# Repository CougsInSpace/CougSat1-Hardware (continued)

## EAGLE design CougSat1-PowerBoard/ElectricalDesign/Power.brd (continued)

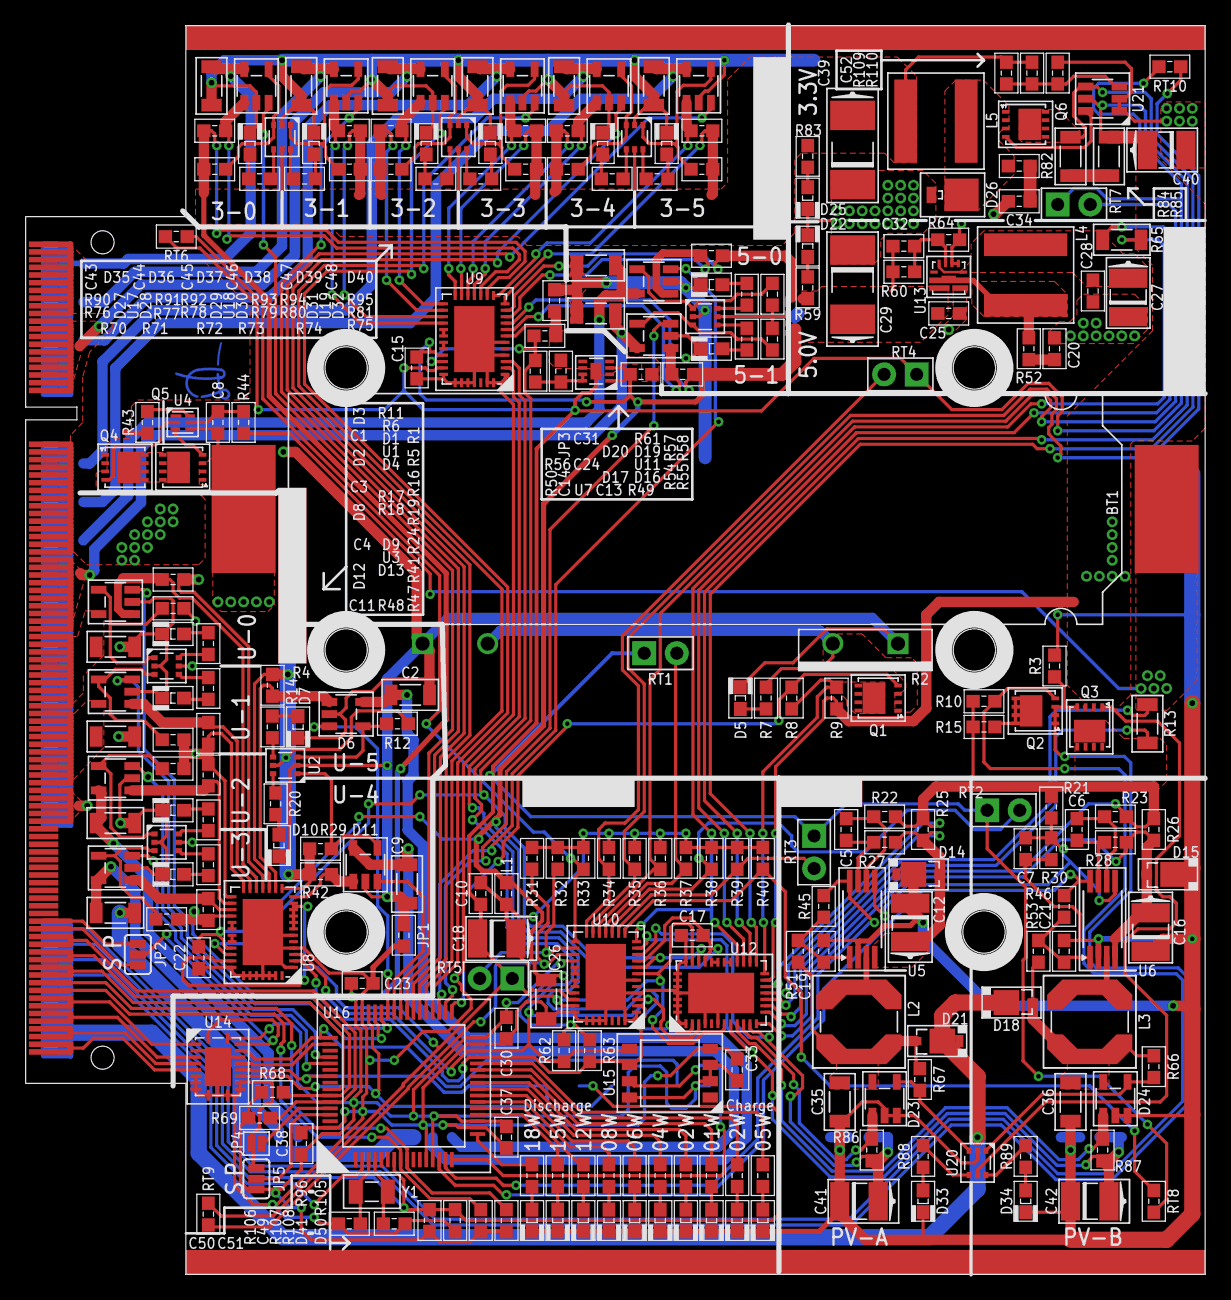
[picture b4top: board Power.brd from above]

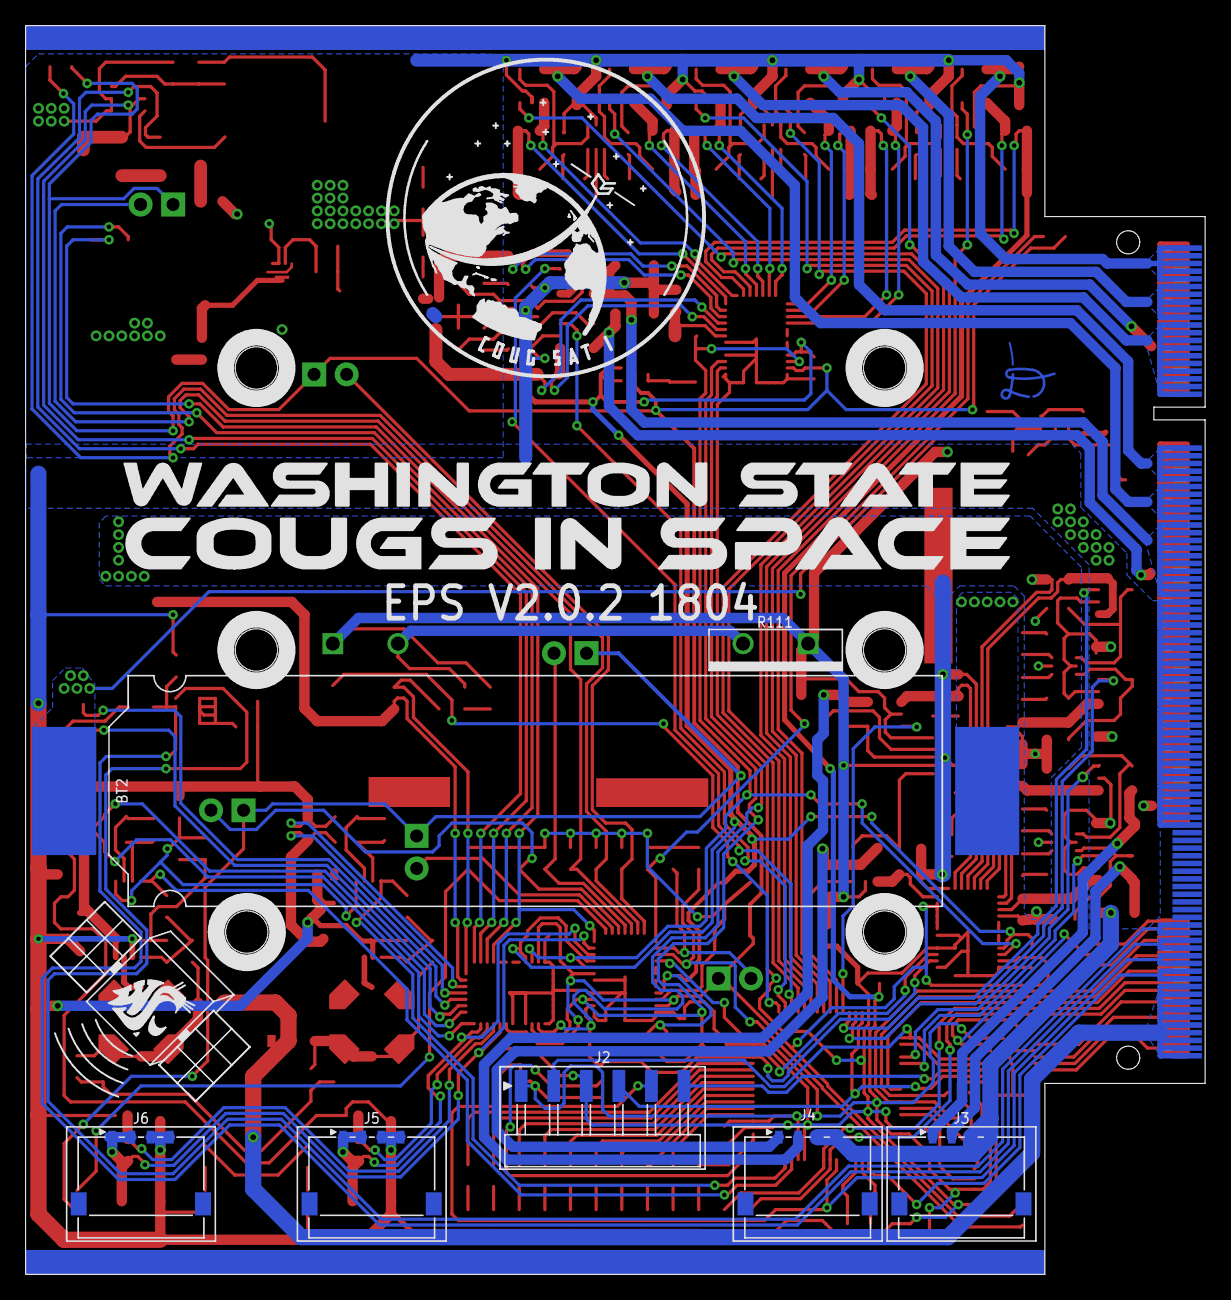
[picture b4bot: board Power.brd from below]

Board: 2 copper layers, 92.0 x 97.4 mm, 279 parts (11 on the bottom side), 209 nets.

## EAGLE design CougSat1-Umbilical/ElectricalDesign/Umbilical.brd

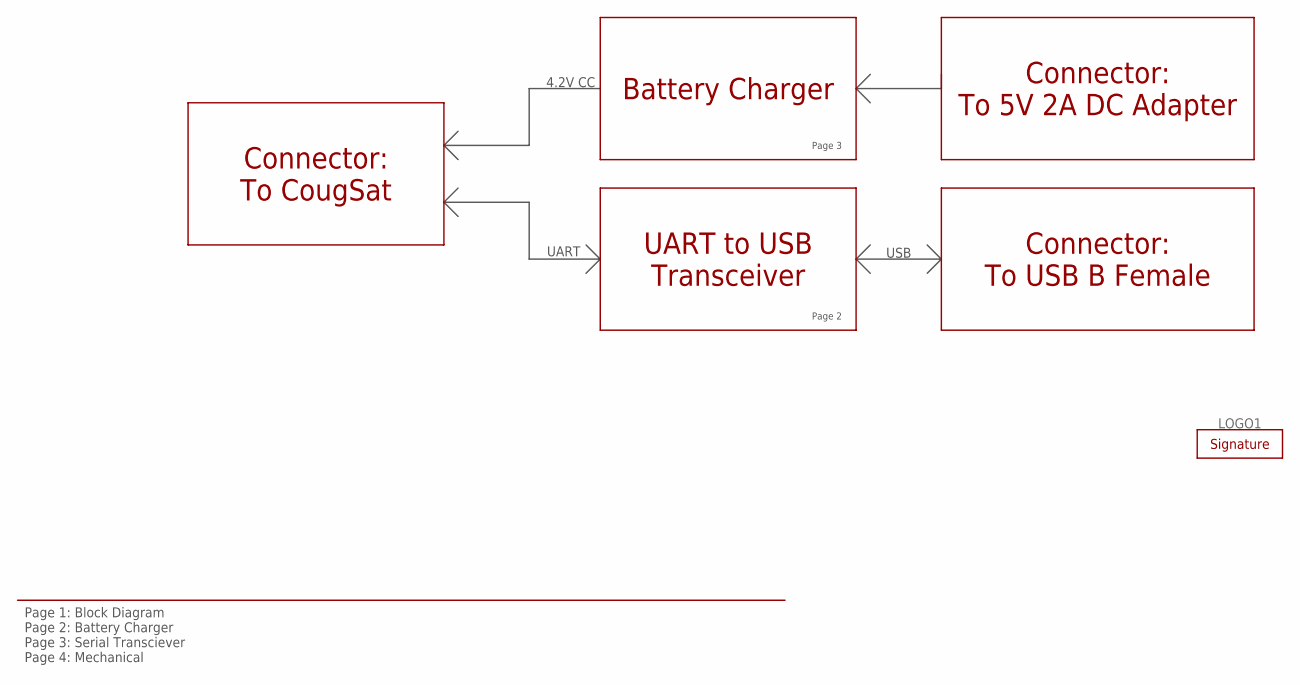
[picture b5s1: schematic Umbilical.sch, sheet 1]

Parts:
LOGO1: SIGNATUREJAYSON; SIGN-JAYSON

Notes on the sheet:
Page 1: Block Diagram Page 2: Battery Charger Page 3: Serial Transciever Page 4: Mechanical
Connector: To CougSat
Battery Charger
UART to USB Transceiver
Connector: To 5V 2A DC Adapter
Connector: To USB B Female
4.2V CC
UART
USB
Page 2
Page 3

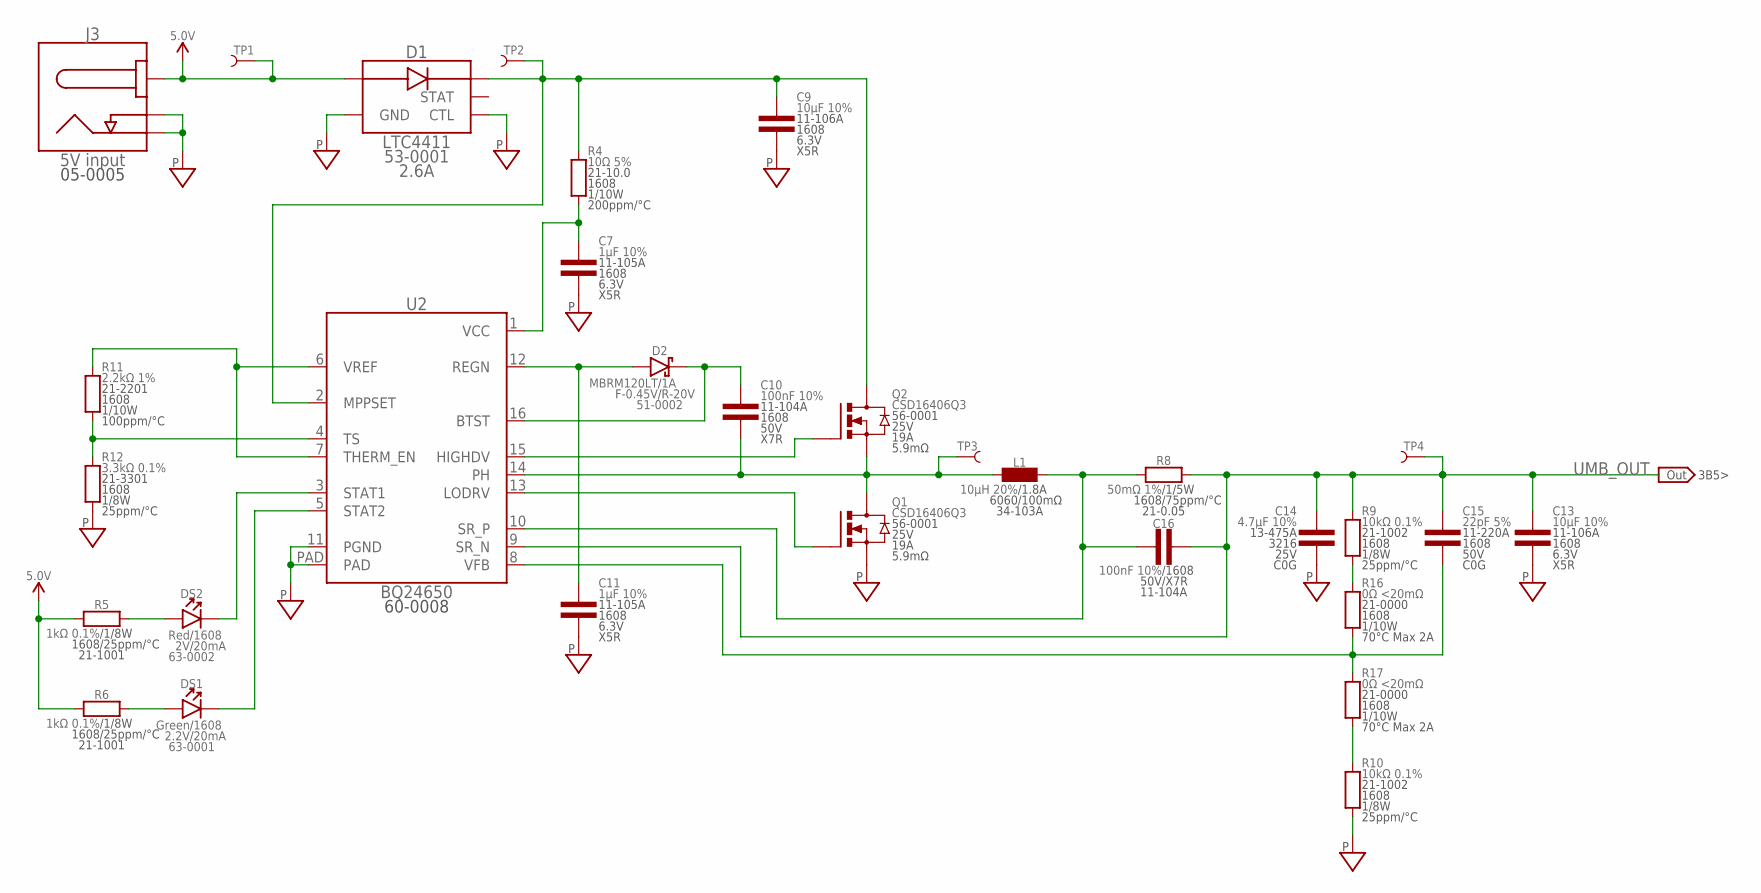
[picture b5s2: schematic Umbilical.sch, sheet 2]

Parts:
C7, C11: 1µF 10%; 1608
C9, C13: 10µF 10%; 1608
C10, C16: 100nF 10%; 1608
C14: 4.7µF 10%; 3216
C15: 22pF 5%; 1608
D1: LTC4411; SOT23-5
D2: MBRM120LT; POWERMITE
DS1: Green; 1608-POL
DS2: Red; 1608-POL
J3: 5V input; BARREL-2.1X5.5-R
L1: 10µH 20%; 6060
Q1, Q2: CSD16406Q3; SON-3333
R4: 10Ω 5%; 1608
R5, R6: 1kΩ 0.1%; 1608
R8: 50mΩ 1%; 1608
R9, R10: 10kΩ 0.1%; 1608
R11: 2.2kΩ 1%; 1608
R12: 3.3kΩ 0.1%; 1608
R16, R17: 0Ω <20mΩ; 1608
TP1, TP2, TP3, TP4: TEST_POINT-THT-1.0; THT-1.0
U2: BQ24650; QFN-16-3535

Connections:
5.0V: D1.1 (IN), J3.1 (CENTER), R5.1, R6.1, TP1.1
BTST: C10.1, D2.C, U2.16 (BTST)
CHARGING_STAT_G: DS1.C, U2.5 (STAT2)
CHARGING_STAT_G_LED: DS1.A, R6.2
CHARGING_STAT_R: DS2.C, U2.3 (STAT1)
CHARGING_STAT_R_LED: DS2.A, R5.2
DIODE_OUT: C9.1, D1.5 (OUT), Q2.5 (D), Q2.6 (D), Q2.7 (D), Q2.8 (D), Q2.PAD (D), R4.2, TP2.1, U2.2 (MPPSET)
FEEDBACK_HIGH: R9.1, R16.2
FEEDBACK_LOW: R10.2, R17.1
HIGHDV: Q2.4 (G), U2.15 (HIGHDV)
LODRV: Q1.4 (G), U2.13 (LODRV)
PGND: C7.2, C9.2, C11.2, C13.2, C14.2, D1.2 (GND), D1.3 (CTL), J3.2 (SLEEVE), J3.3 (SW), Q1.1 (S), Q1.2 (S), Q1.3 (S), R10.1, R12.1, U2.11 (PGND), U2.PAD; also elsewhere on the board
PH: C10.2, L1.1, Q1.5 (D), Q1.6 (D), Q1.7 (D), Q1.8 (D), Q1.PAD (D), Q2.1 (S), Q2.2 (S), Q2.3 (S), TP3.1, U2.14 (PH)
REGN: C11.1, D2.A, U2.12 (REGN)
SR_P: C16.1, L1.2, R8.1, U2.10 (SR_P)
TS: R11.1, R12.2, U2.4 (TS)
UMB_OUT: C13.1, C14.1, C15.1, C16.2, R8.2, R9.2, TP4.1, U2.9 (SR_N); also elsewhere on the board
VCC: C7.1, R4.1, U2.1 (VCC)
VFB: C15.2, R16.1, R17.2, U2.8 (VFB)
VREF: R11.2, U2.6 (VREF), U2.7 (THERM_EN)

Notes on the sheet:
3B5>

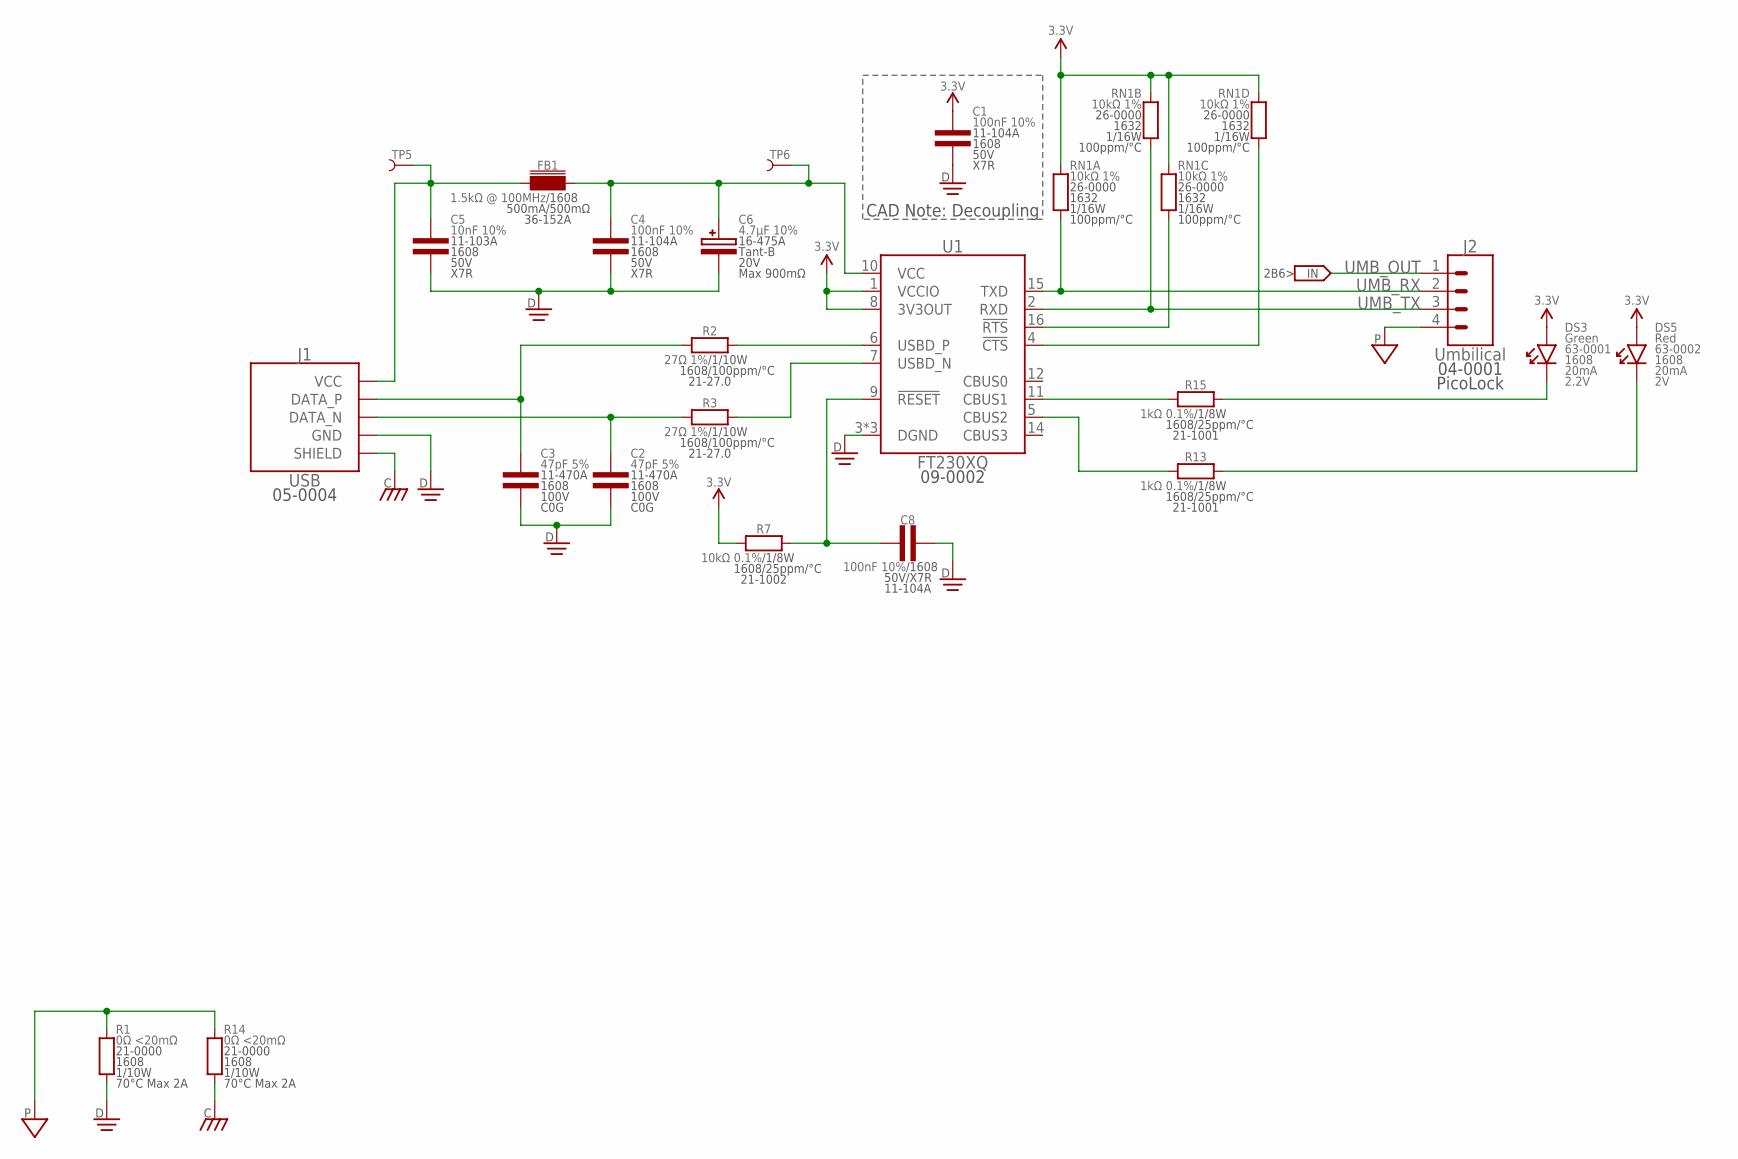
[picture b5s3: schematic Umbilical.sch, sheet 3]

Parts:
C1, C4, C8: 100nF 10%; 1608
C2, C3: 47pF 5%; 1608
C5: 10nF 10%; 1608
C6: 4.7µF 10%; 4028-POL
DS3: Green; 1608-POL
DS5: Red; 1608-POL
FB1: 1.5kΩ @ 100MHz; 1608
J1: USB; USB-B-FEMALE
J2: Umbilical; PICOLOCK1.5-04
R1, R14: 0Ω <20mΩ; 1608
R2, R3: 27Ω 1%; 1608
R7: 10kΩ 0.1%; 1608
R13, R15: 1kΩ 0.1%; 1608
RN1: 10kΩ 1%; 1632
TP5, TP6: TEST_POINT-THT-1.0; THT-1.0
U1: FT230XQ; QFN-16-4040

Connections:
3.3V: C1.1, DS3.A, DS5.A, R7.1, RN1.5 (2), RN1.6 (2), RN1.7 (2), RN1.8 (2), U1.1 (VCCIO), U1.8 (3V3OUT)
!CTS: RN1.4 (1), U1.4 (!CTS)
!RTS: RN1.3 (1), U1.16 (!RTS)
CBUS1: R15.1, U1.11 (CBUS1)
CBUS2: R13.1, U1.5 (CBUS2)
CHASSIS: J1.SHIELD@1 (SHIELD), J1.SHIELD@2 (SHIELD), R14.1
DGND: C1.2, C2.2, C3.2, C4.2, C5.2, C6.C, C8.2, J1.4 (GND), R1.1, U1.3 (DGND), U1.13 (DGND), U1.PAD (DGND)
PGND: J2.4, R1.2, R14.2; also elsewhere on the board
RXLED_C: DS5.C, R13.2
TXLED_C: DS3.C, R15.2
UMB_OUT: J2.1; also elsewhere on the board
UMB_RX: J2.2, RN1.1, U1.15 (TXD)
UMB_TX: J2.3, RN1.2 (1), U1.2 (RXD)
USB5V: C5.1, FB1.1, J1.1 (VCC), TP5.1
USB5V_FILTERED: C4.1, C6.A, FB1.2, TP6.1, U1.10 (VCC)
USB_CONN_N: C2.1, J1.2 (DATA_N), R3.1
USB_CONN_P: C3.1, J1.3 (DATA_P), R2.1
USB_N: R3.2, U1.7 (USBD_N)
USB_P: R2.2, U1.6 (USBD_P)
USB_RESET: C8.1, R7.2, U1.9 (!RESET)

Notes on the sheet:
CAD Note: Decoupling
2B6>

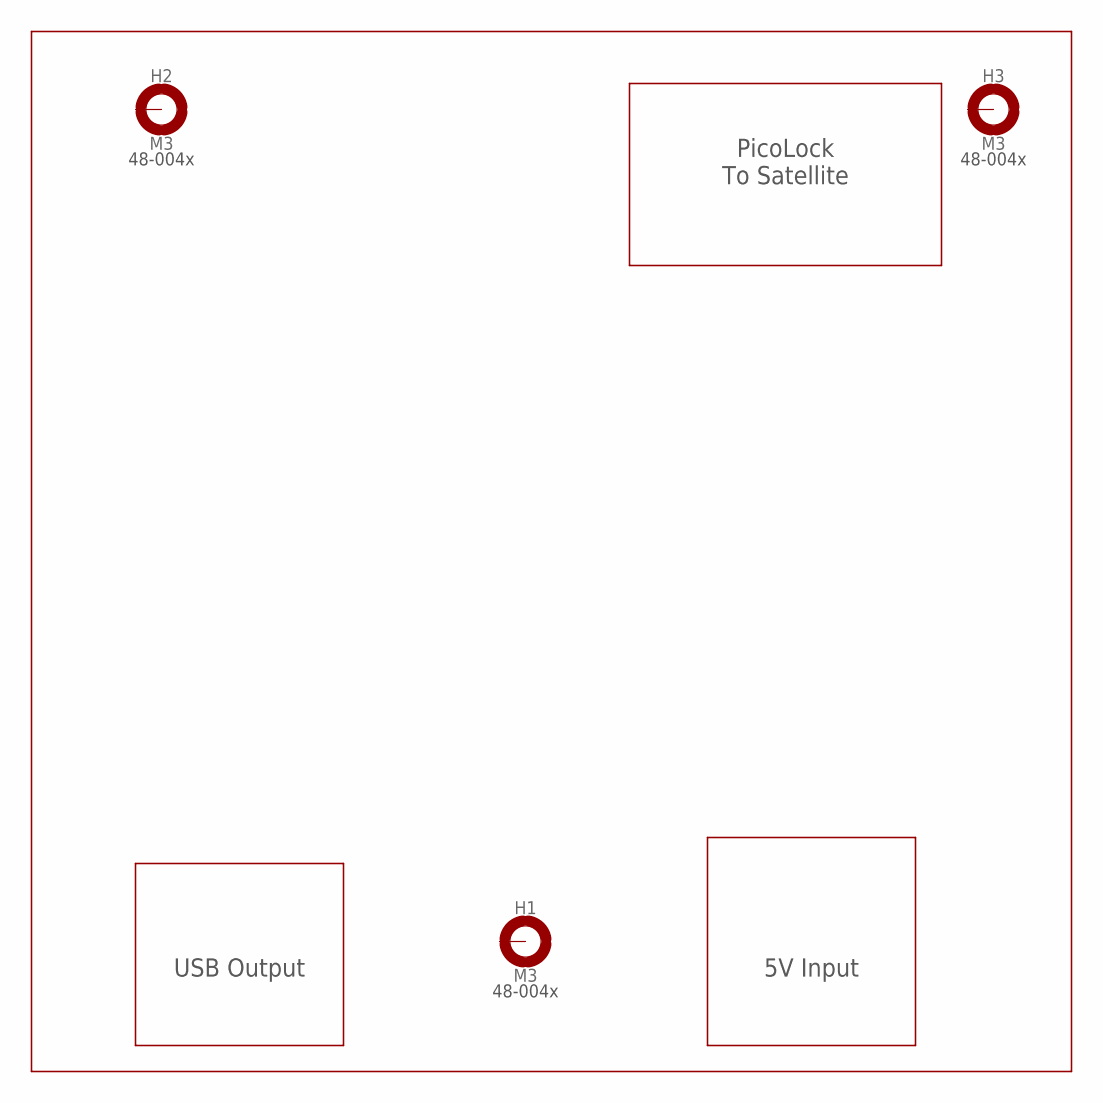
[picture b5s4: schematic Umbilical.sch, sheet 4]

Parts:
H1, H2, H3: M3; MOUNTING_HOLE-3.3

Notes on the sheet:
PicoLock To Satellite
5V Input
USB Output

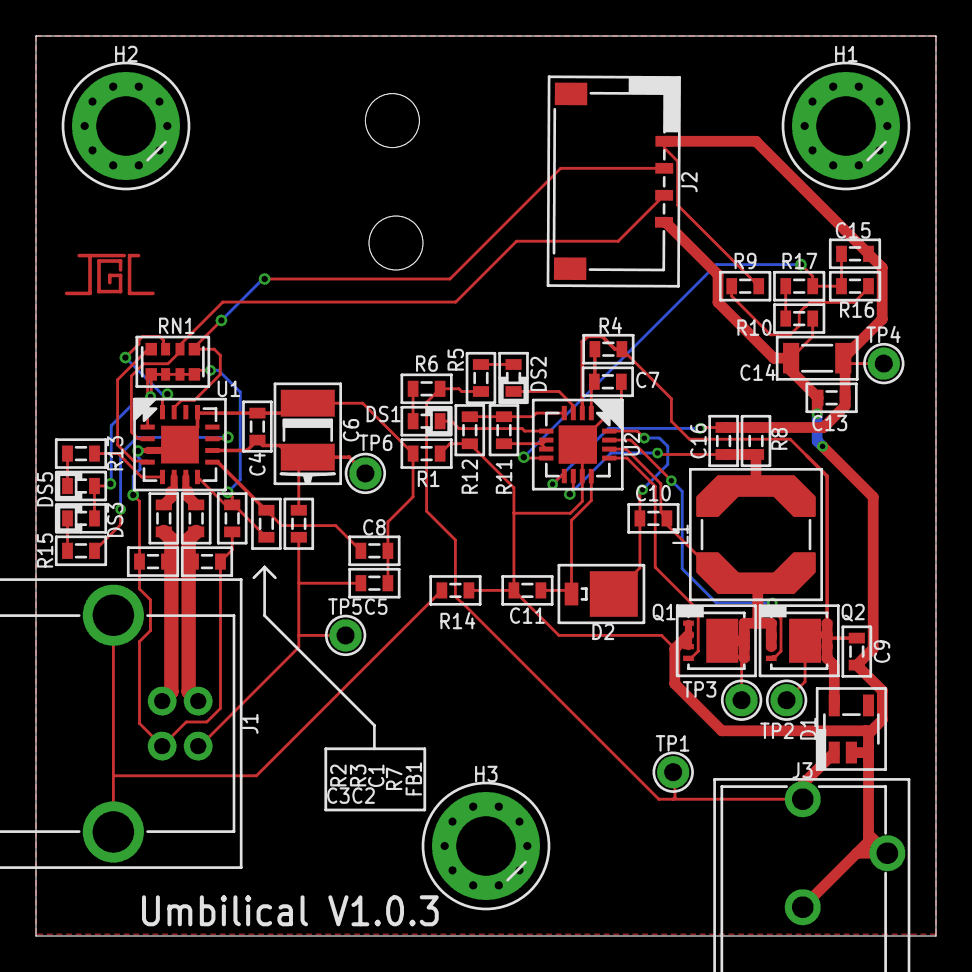
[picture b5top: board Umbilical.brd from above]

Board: 2 copper layers, 50.0 x 50.0 mm, 58 parts (0 on the bottom side), 38 nets.
